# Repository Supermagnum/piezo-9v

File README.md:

# piezo-9v
A small PCB for pizoelectric amplifier, runs on 9V.
It should have battery capacity for around 5 hours.

It's fairly easy and straight forward to solder the components to the circuit board, a nice pointy soldering iron, solder,and a ohm or multimeter is all that is needed. 

Please use 0,5 W metal film resistors with 1% tolerance or better and audio quality capacitors.
C0G (NP0) or X7R capacitors is very good.

Of course one needs a suitable metal box, and the circuit boards components must not come in contact with the metal box. 
That will cause short circuit, so it's best mounted on conducting stand offs because the corner pads on the PCB board must be connected to the metal box.
Check that no one of the soldering pads has been bridged before applying power.

A shielded cable must be used to connect to the piezoelectric element.
NOTE:
It is my opinion that a shielded cable with 2 conductors inside is the best.
Suggested cable: Digi-Key Part Number: 30-01225-5-ND

The sensivity can be made adjustable if a rotary potentiometer is used to replace R7.
A nice one is : Digi-Key Part Number 310Y-001-103L-ND. 
Connect one end of the terminals to one of the R7 solder points, and the middle terminal to the other. 

It can be used for a reverb plate, listening to the insides of a engine,recording the sound of vibrating things. 
You will need one piezoelectric disk for that, mounted in a metal box made of thin metal. Non electric conductive super glue is useable for that. 
Just glue it to a flat surface. 
The piezoelectric disk should be electrically insulated from the metal box.

Picture of a piezoelectric disc, with red wire for positive polarity and black for negative: https://github.com/Supermagnum/piezo-balanced/blob/main/Piezo-element-6.jpg

Schematic diagram:
https://github.com/Supermagnum/piezo-9v/blob/main/9v-preamp.pdf
D1 is a LED that lights up when it's switched on.

Aisler PCB:
https://aisler.net/p/BZUXMWVU

Digikey part list:
https://github.com/Supermagnum/piezo-9v/blob/main/9vpiezo-digikey-BOM.csv
(does NOT include the PCB or the necessary two conductor shielded cable to the piezoelectric element)

Component side of PCB:
https://github.com/Supermagnum/piezo-9v/blob/main/front.jpg

Back side:
https://github.com/Supermagnum/piezo-9v/blob/main/back.jpg

Picture with sockets for the opamps, capacitators,resistors and diodes installed:
https://github.com/Supermagnum/piezo-9v/blob/main/9v-preamp-components.jpg

Gerber files:
https://github.com/Supermagnum/piezo-9v/tree/main/gerbers

Some methods of mounting a piezoelectric disk can be found here:
https://locusonus.org/wiki/index.php?page=Hydrophone.en
Use a metal box with thin walls.
Commercial ones uses kerosene oil, so olive oil or sunflower oil is a great alternative as it will not pollute the environment if any leaks occurs. Aquarium silicone can also be used.
For flowing water a streamlined bulb is best, it reduces flow noise.

Around 35 to 40 dB gain should be nice for hydrophone usage.

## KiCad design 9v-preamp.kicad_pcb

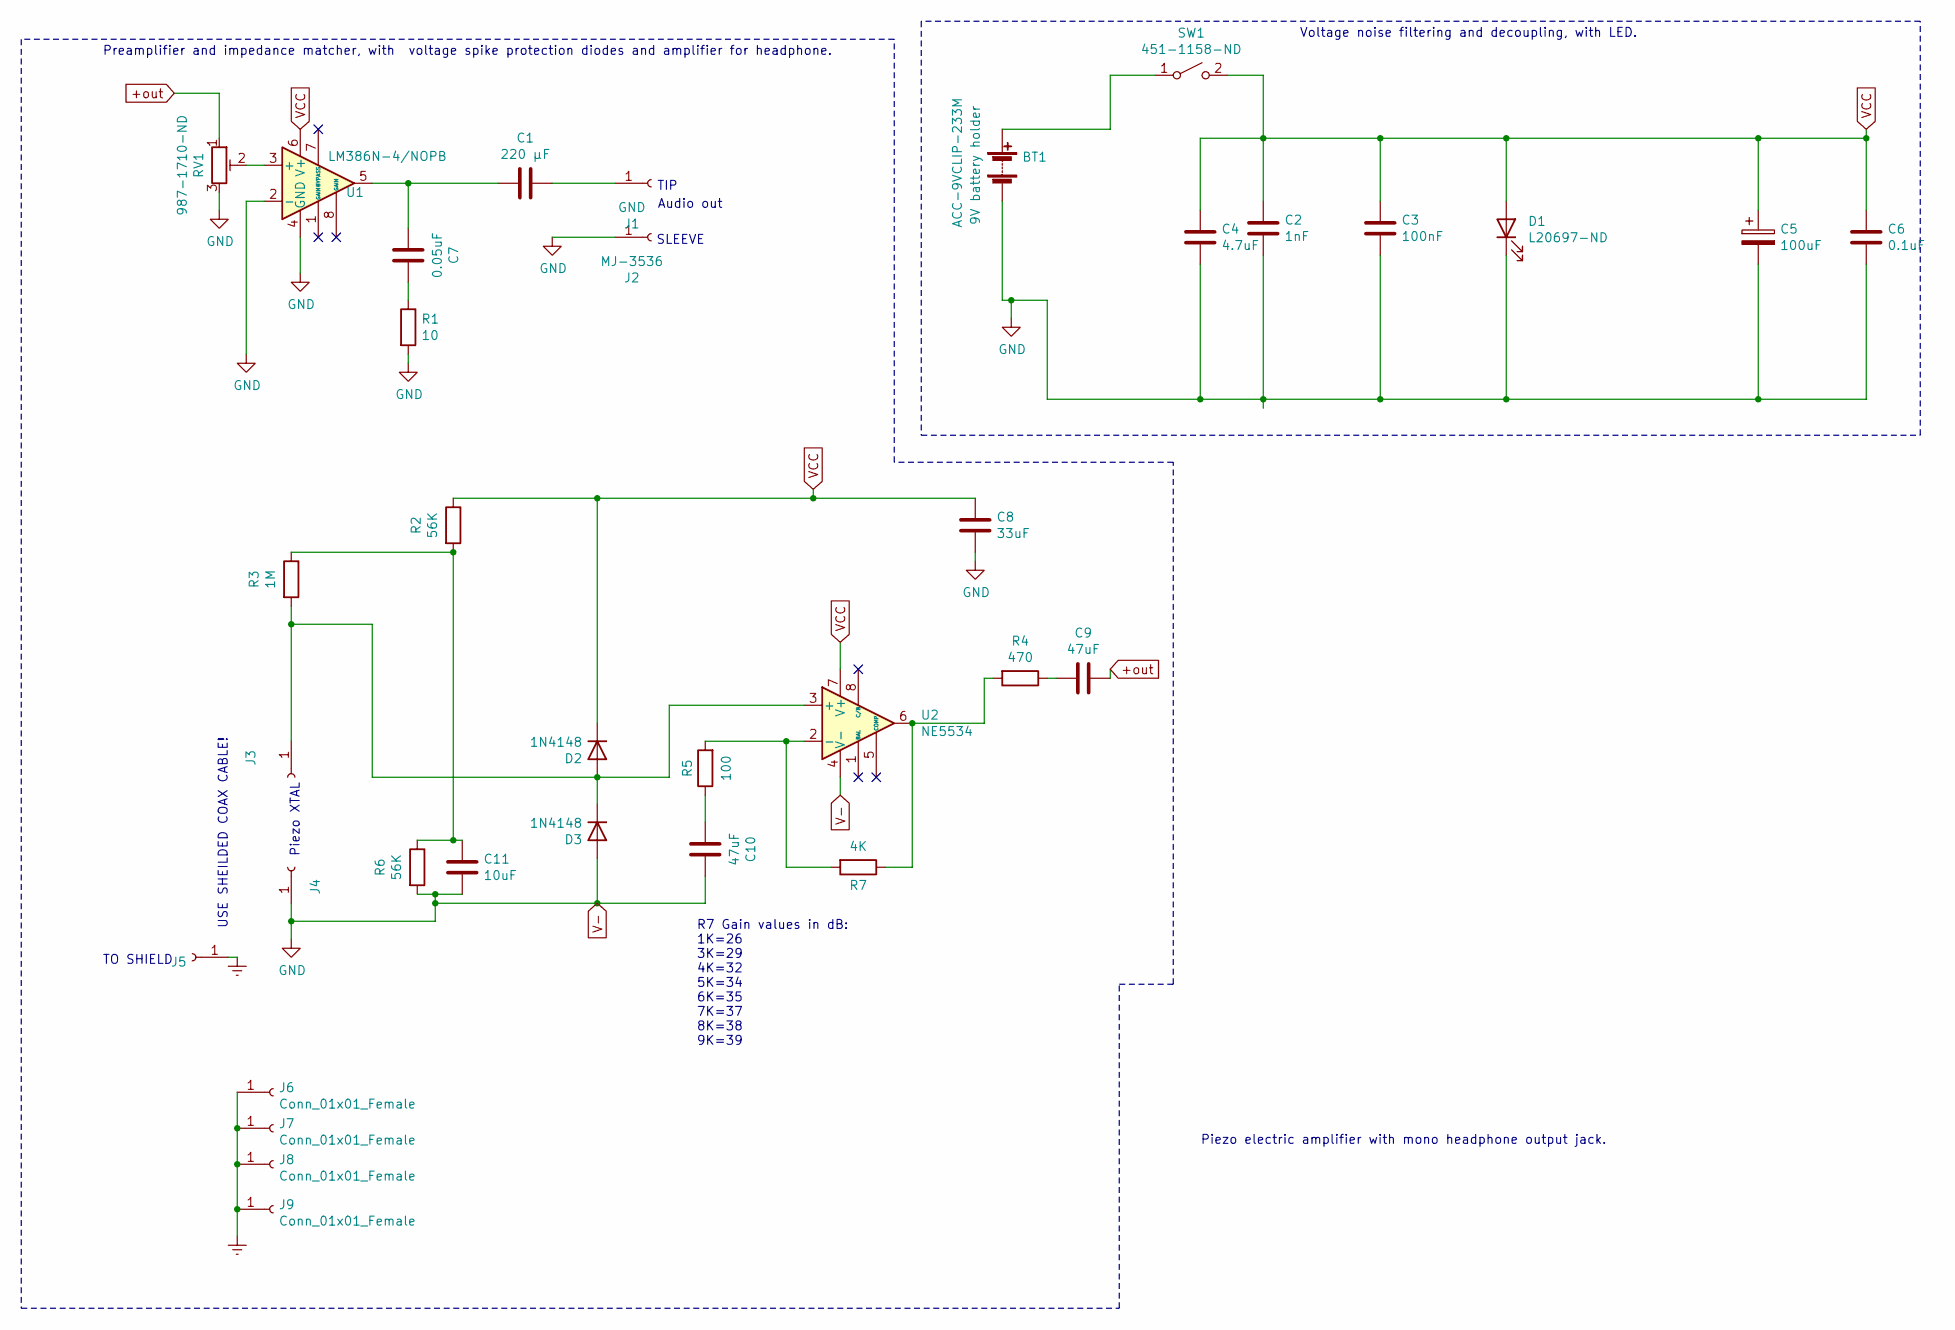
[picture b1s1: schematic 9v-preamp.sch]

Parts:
BT1: ACC-9VCLIP-233M; PinHeader_1x02_P2.54mm_Vertical
C1: 220 µF; CP_Radial_D6.3mm_P2.50mm
C2: 1nF; C_Disc_D3.8mm_W2.6mm_P2.50mm
C3: 100nF; C_Disc_D3.8mm_W2.6mm_P2.50mm
C4: 4.7uF; C_Disc_D3.8mm_W2.6mm_P2.50mm
C5: 100uF; CP_Radial_D8.0mm_P3.50mm
C6: 0.1uF; C_Disc_D3.8mm_W2.6mm_P2.50mm
C7: 0.05uF; C_Disc_D3.8mm_W2.6mm_P2.50mm
C8: 33uF; C_Disc_D5.0mm_W2.5mm_P2.50mm
C9, C10: 47uF; C_Disc_D5.0mm_W2.5mm_P2.50mm
C11: 10uF; C_Disc_D5.0mm_W2.5mm_P2.50mm
D1: L20697-ND; LED_D2.0mm_W4.8mm_H2.5mm_FlatTop
D2, D3: 1N4148; D_DO-35_SOD27_P7.62mm_Horizontal
J1: GND; MountingHole_2.2mm_M2_DIN965_Pad
J2: MJ-3536; MountingHole_2.2mm_M2_DIN965_Pad
J3, J4: Conn_01x01_Female; MountingHole_2.2mm_M2_ISO7380_Pad
J5, J6, J7, J8, J9: Conn_01x01_Female; MountingHole_2.2mm_M2_DIN965_Pad
R1: 10; R_Axial_DIN0207_L6.3mm_D2.5mm_P7.62mm_Horizontal
R2, R6: 56K; R_Axial_DIN0204_L3.6mm_D1.6mm_P5.08mm_Horizontal
R3: 1M; R_Axial_DIN0204_L3.6mm_D1.6mm_P5.08mm_Horizontal
R4: 470; R_Axial_DIN0204_L3.6mm_D1.6mm_P5.08mm_Horizontal
R5: 100; R_Axial_DIN0204_L3.6mm_D1.6mm_P5.08mm_Horizontal
R7: 4K; R_Axial_DIN0204_L3.6mm_D1.6mm_P5.08mm_Horizontal
RV1: 987-1710-ND; PinHeader_1x03_P2.54mm_Vertical
SW1: 451-1158-ND; PinHeader_2x01_P2.00mm_Vertical
U1: LM386N-4/NOPB; DIP-8_W7.62mm_Socket
U2: NE5534; DIP-8_W7.62mm_Socket

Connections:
+out: C9.1, RV1.1
Earth: J5.1, J6.1, J7.1, J8.1, J9.1
unnamed: BT1.1 (+), SW1.1 (A)
unnamed: C1.1, J1.1
unnamed: C1.2, C7.2, U1.5
unnamed: C7.1, R1.1
unnamed: C9.2, R4.1
unnamed: C10.2, R5.1
unnamed: C11.1, R2.2, R3.1, R6.1
unnamed: D2.2 (A), D3.1 (K), J3.1, R3.2, U2.3 (+)
unnamed: R4.2, R7.1, U2.6
unnamed: R5.2, R7.2, U2.2 (-)
unnamed: RV1.2, U1.3 (+)
V-: BT1.2 (-), C2.1, C3.1, C4.2, C5.2, C6.1, C8.2, C10.1, C11.2, D1.1 (K), D3.2 (A), J2.1, J4.1, R1.2, R6.2, RV1.3, U1.2 (-), U1.4 (GND), U2.4 (V-)
VCC: C2.2, C3.2, C4.1, C5.1, C6.2, C8.1, D1.2 (A), D2.1 (K), R2.1, SW1.2 (B), U1.6 (V+), U2.7 (V+)

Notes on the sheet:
Piezo electric amplifier with mono headphone output jack.
Audio out
TIP
SLEEVE
Piezo XTAL
R7 Gain values in dB: 1K=26 3K=29 4K=32 5K=34 6K=35 7K=37 8K=38 9K=39
USE SHEILDED COAX CABLE!
TO SHIELD
Voltage noise filtering and decoupling, with LED.
Preamplifier and impedance matcher, with voltage spike protection diodes and amplifier for headphone.

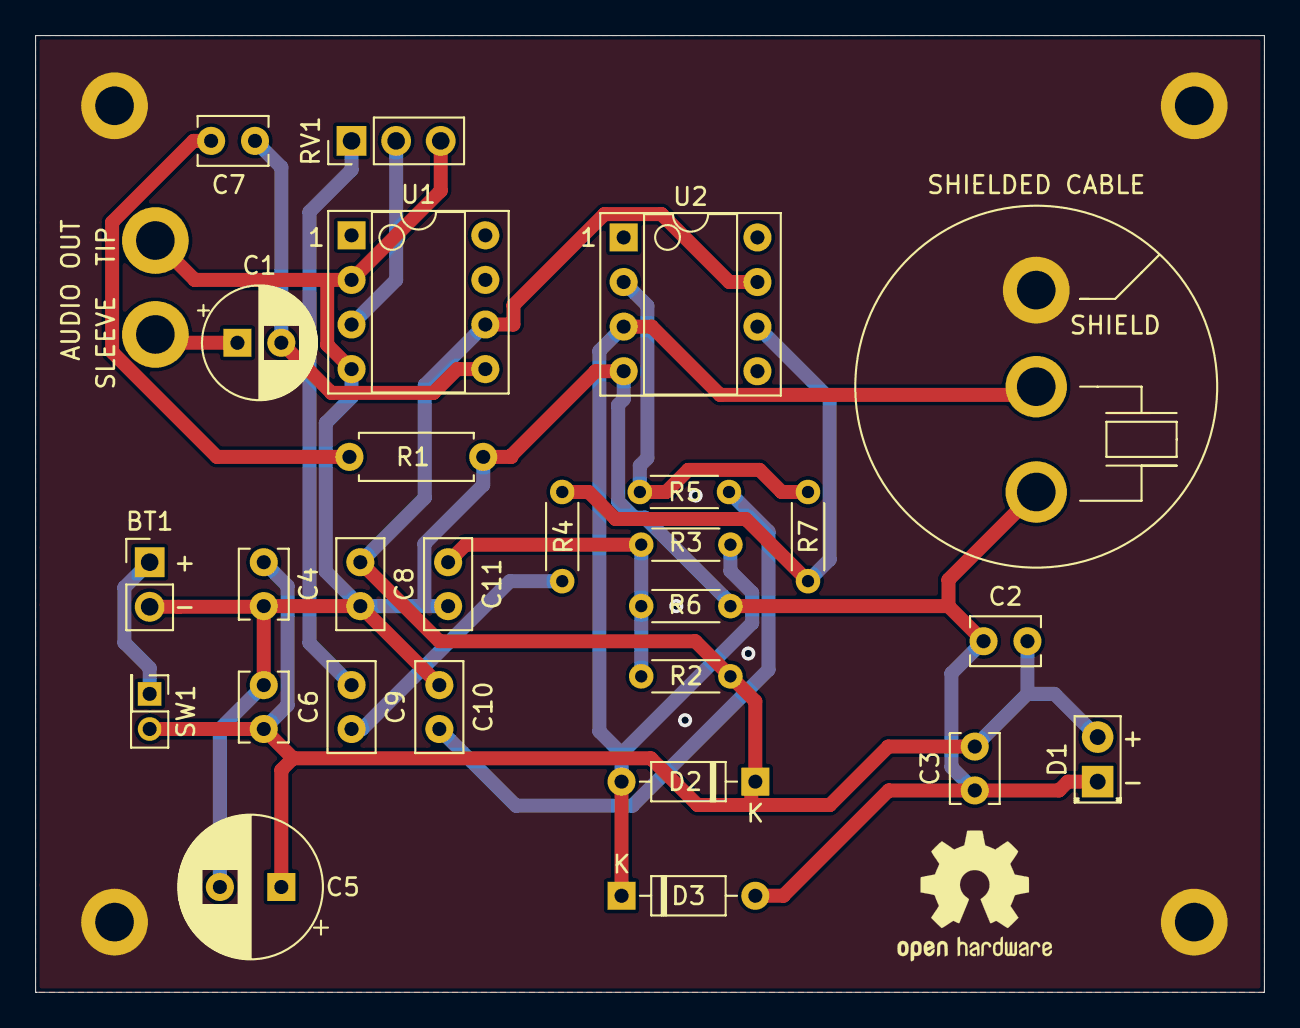
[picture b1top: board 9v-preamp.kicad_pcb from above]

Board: 2 copper layers, 70.0 x 54.5 mm, 35 parts (0 on the bottom side), 15 nets.

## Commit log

2021-06-28 Add files via upload
    updated files, turned U1 around so It faces the same way as U2.
2021-06-28 Added digikey part list.
2021-07-02 Add files via upload
    corrected missing connection to VCC.
2021-07-21 Add files via upload
    Added + and - marks on the LED solder connections, and pin 1 on the op amps.
